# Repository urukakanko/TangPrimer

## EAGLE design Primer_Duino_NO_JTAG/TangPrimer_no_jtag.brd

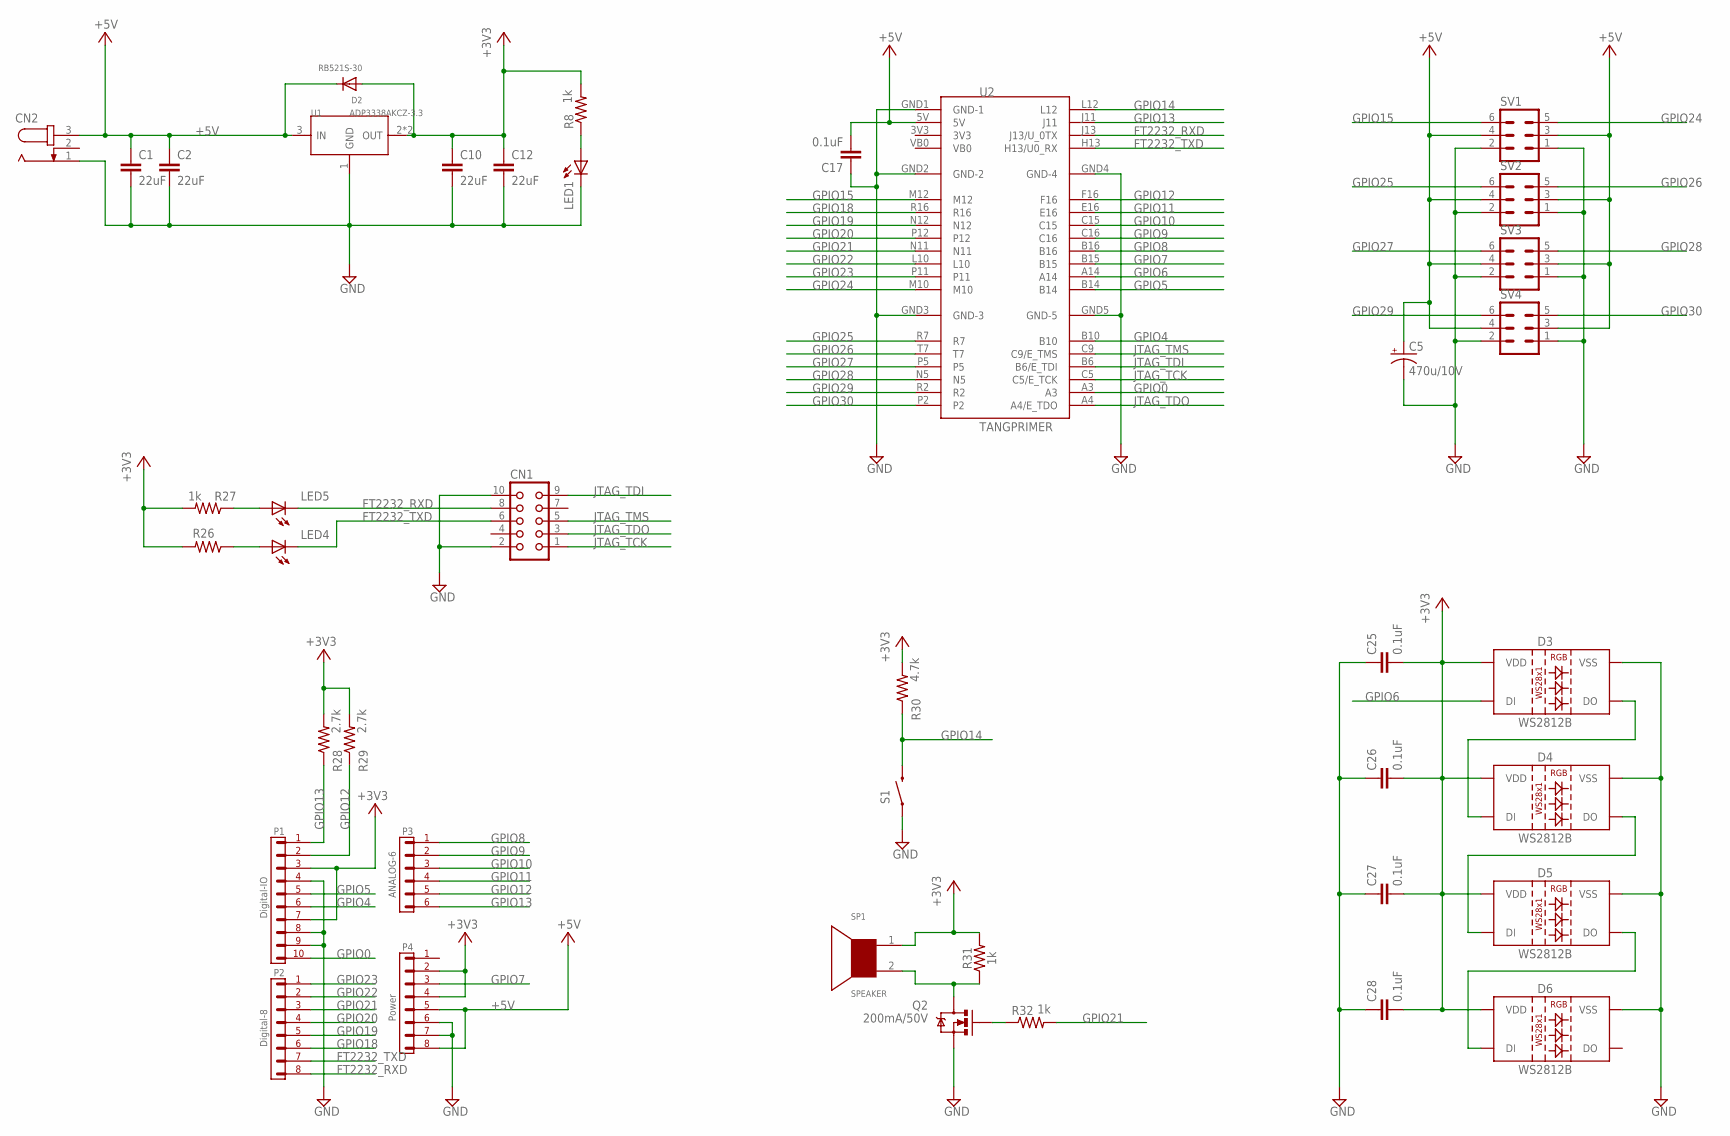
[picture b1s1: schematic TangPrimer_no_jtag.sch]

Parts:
C1, C2, C10, C12: 22uF; 0603
C5: 470u/10V; E2,5-7
C17, C25, C26, C27, C28: 0.1uF; 0603
CN1: CON10
CN2: JACK-PLUG0; SPC4077
D2: RB521S-30; SOD-523
D3, D4, D5, D6: WS2812B; WS2812_2020
LED1, LED4, LED5: LEDCHIP-LED0805; CHIP-LED0805
Q2: 200mA/50V; SOT23-3
R8, R26, R27, R31, R32: 1k; 0603
R28, R29: 2.7k; 0603
R30: 4.7k; 0603
S1: SWITCH-MOMENTARY-2SMD-1101NE; TACTILE-SWITCH-1101NE
S2: TANGPRIMER_BASE
SP1: SPEAKER
SV1, SV2, SV3, SV4: MA03-2
U1: ADP3338AKCZ-3.3; SOT-223
U2: TANGPRIMER

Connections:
+3V3: C10.1, C12.1, C25.2, C26.2, C27.2, C28.2, D2.A, D3.4 (VDD), D4.4 (VDD), D5.4 (VDD), D6.4 (VDD), R8.2, R26.2, R27.2, R28.2, R29.2, R30.2, R31.2, S2.3V3-1, S2.3V3-2, S2.AREF, S2.D11, SP1.1, U1.2 (OUT), U1.TER (OUT)
+5V: C1.1, C2.1, C5.+, C17.2, CN2.3, D2.K (C), S2.5V, S2.VIN, SV1.3, SV1.4, SV2.3, SV2.4, SV3.3, SV3.4, SV4.3, SV4.4, U1.3 (IN), U2.5V
FT2232_RXD: CN1.8, LED5.C, S2.RXD (RX), U2.J13 (J13/U_0TX)
FT2232_TXD: CN1.6, LED4.C, S2.TXD (TX), U2.H13 (H13/U0_RX)
GND: C1.2, C2.2, C5.-, C10.2, C12.2, C17.1, C25.1, C26.1, C27.1, C28.1, CN1.2, CN1.10, CN2.1, D3.2 (VSS), D4.2 (VSS), D5.2 (VSS), D6.2 (VSS), LED1.C, Q2.2 (S), S1.1, S2.D9, S2.D10, S2.GND-1 (GND1), S2.GND-2 (GND2), S2.GND-3 (GND3), SV1.1, SV1.2, SV2.1, SV2.2, SV3.1, SV3.2, SV4.1, SV4.2, U1.1 (GND), U2.GND1 (GND-1), U2.GND2 (GND-2), U2.GND3 (GND-3), U2.GND4 (GND-4), U2.GND5 (GND-5)
GPIO0: S2.D8, U2.A3
GPIO4: S2.D12, U2.B10
GPIO5: S2.D13, U2.B14
GPIO6: D3.3 (DI), U2.A14
GPIO7: S2.RESET, U2.B15
GPIO8: S2.A0, U2.B16
GPIO9: S2.A1, U2.C16
GPIO10: S2.A2, U2.C15
GPIO11: S2.A3, U2.E16
GPIO12: R29.1, S2.A4, S2.SDA, U2.F16
GPIO13: R28.1, S2.A5, S2.SCL, U2.J11
GPIO14: R30.1, S1.2, U2.L12
GPIO15: SV1.6, U2.M12
GPIO18: S2.D2, U2.R16
GPIO19: S2.D3, U2.N12
GPIO20: S2.D4, U2.P12
GPIO21: R32.2, S2.D5, U2.N11
GPIO22: S2.D6, U2.L10
GPIO23: S2.D7, U2.P11
GPIO24: SV1.5, U2.M10
GPIO25: SV2.6, U2.R7
GPIO26: SV2.5, U2.T7
GPIO27: SV3.6, U2.P5
GPIO28: SV3.5, U2.N5
GPIO29: SV4.6, U2.R2
GPIO30: SV4.5, U2.P2
JTAG_TCK: CN1.1, U2.C5 (C5/E_TCK)
JTAG_TDI: CN1.9, U2.B6 (B6/E_TDI)
JTAG_TDO: CN1.3, U2.A4 (A4/E_TDO)
JTAG_TMS: CN1.5, U2.C9 (C9/E_TMS)
unnamed: Q2.3 (D), R31.1, SP1.2
unnamed: Q2.1 (G), R32.1
unnamed: LED1.A, R8.1
unnamed: LED4.A, R26.1
unnamed: LED5.A, R27.1
unnamed: D3.1 (DO), D4.3 (DI)
unnamed: D4.1 (DO), D5.3 (DI)
unnamed: D5.1 (DO), D6.3 (DI)

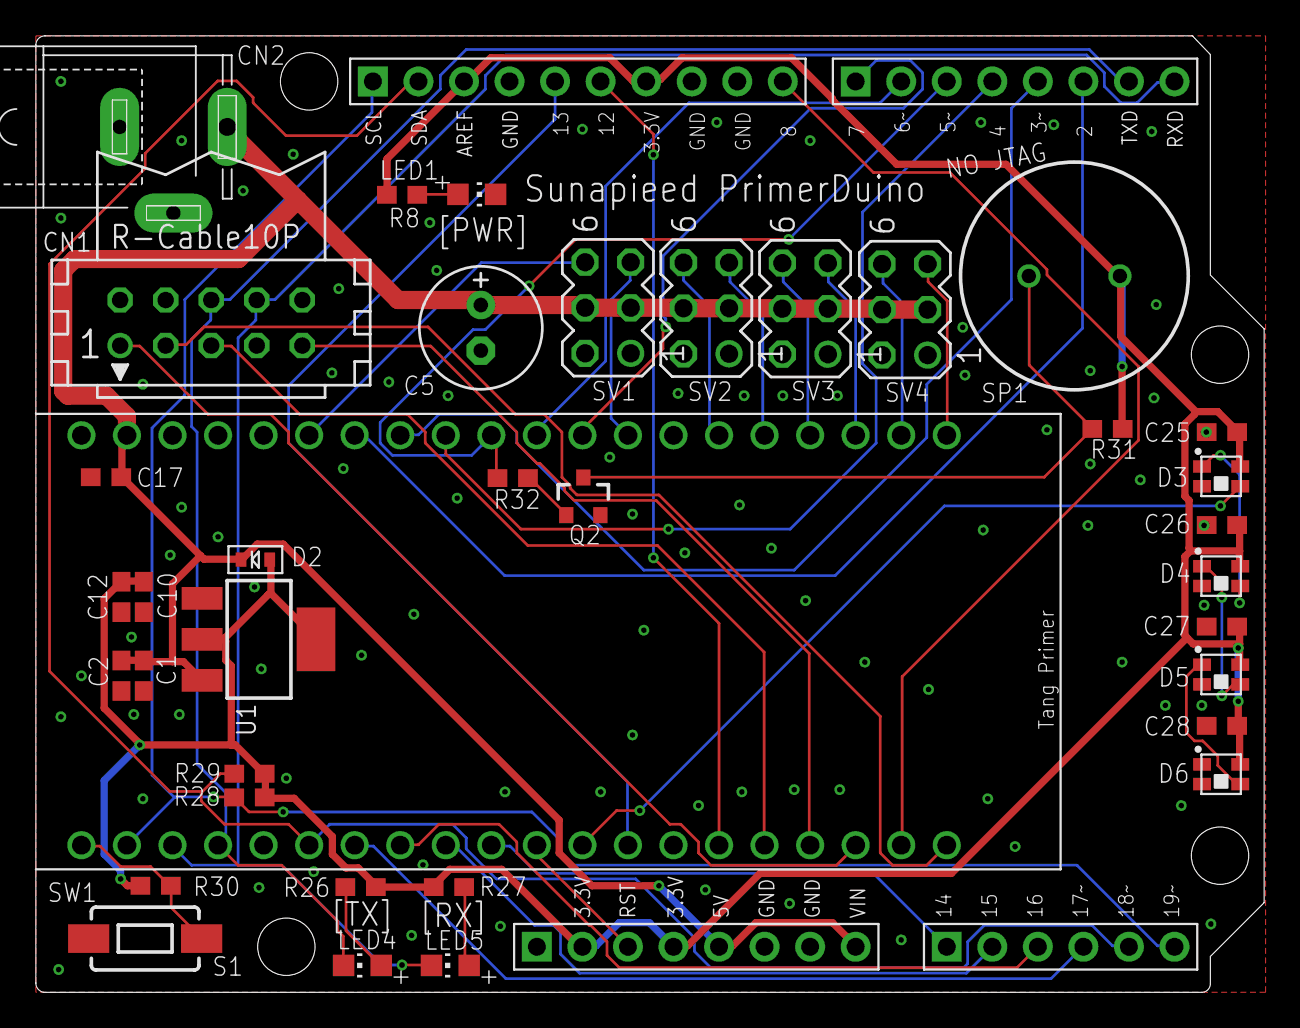
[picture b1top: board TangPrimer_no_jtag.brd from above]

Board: 2 copper layers, 68.5 x 53.3 mm, 38 parts (1 on the bottom side), 43 nets.

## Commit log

2020-04-19 サーボモータ回路(Ver0.01)
2020-04-19 16bitバージョン
2020-05-07 PrimerDuino

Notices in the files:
parts and their libraries:
SparkFun-DiscreteSemi: Licensing: Creative Commons ShareAlike 4.0 International - https://creativecommons.org/licenses/by-sa/4.0
